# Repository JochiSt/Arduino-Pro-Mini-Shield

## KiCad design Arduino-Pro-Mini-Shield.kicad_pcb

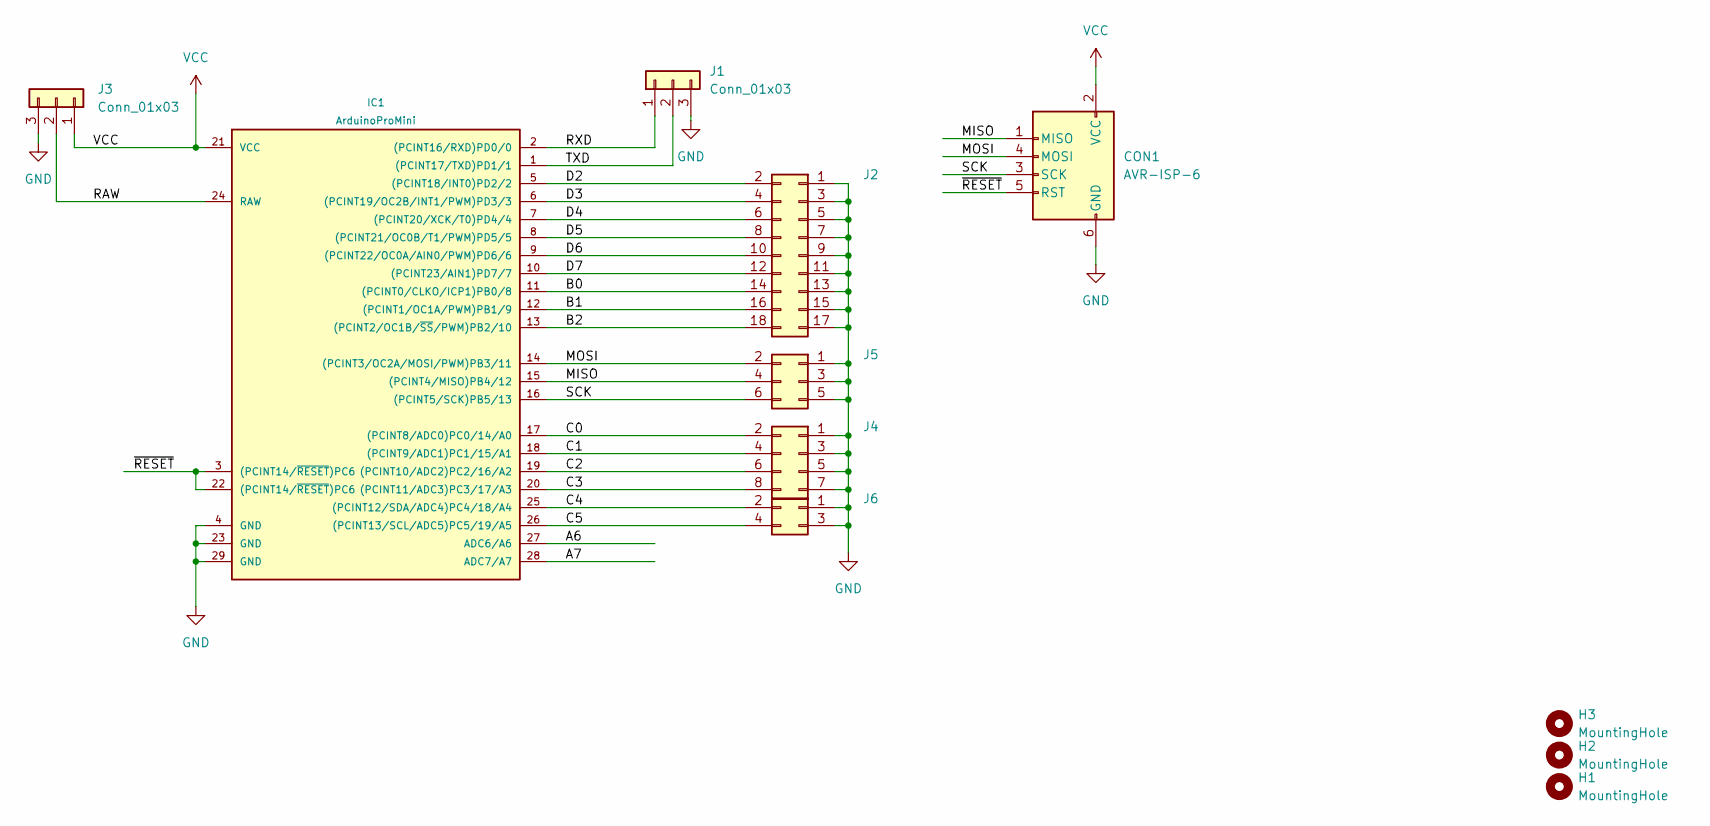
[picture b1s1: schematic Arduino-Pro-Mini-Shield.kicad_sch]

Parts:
CON1: AVR-ISP-6; PinHeader_2x03_P2.54mm_Vertical
H1, H2, H3: MountingHole; MountingHole_3.2mm_M3
IC1: ArduinoProMini; pro_mini
J1, J3: Conn_01x03; PinHeader_1x03_P2.54mm_Vertical
J2: Conn_02x09_Odd_Even; PinHeader_2x09_P2.54mm_Vertical
J4: Conn_02x04_Odd_Even; PinHeader_2x04_P2.54mm_Vertical
J5: Conn_02x03_Odd_Even; PinHeader_2x03_P2.54mm_Vertical
J6: Conn_02x02_Odd_Even; PinHeader_2x02_P2.54mm_Vertical

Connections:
/A6: IC1.27 (ADC6/A6)
/A7: IC1.28 (ADC7/A7)
/B0: IC1.11 ((PCINT0/CLKO/ICP1)PB0/8), J2.14
/B1: IC1.12 ((PCINT1/OC1A/PWM)PB1/9), J2.16
/B2: IC1.13 ((PCINT2/OC1B/~SS/PWM)PB2/10), J2.18
/C0: IC1.17 ((PCINT8/ADC0)PC0/14/A0), J4.2
/C1: IC1.18 ((PCINT9/ADC1)PC1/15/A1), J4.4
/C2: IC1.19 ((PCINT10/ADC2)PC2/16/A2), J4.6
/C3: IC1.20 ((PCINT11/ADC3)PC3/17/A3), J4.8
/C4: IC1.25 ((PCINT12/SDA/ADC4)PC4/18/A4), J6.2
/C5: IC1.26 ((PCINT13/SCL/ADC5)PC5/19/A5), J6.4
/D2: IC1.5 ((PCINT18/INT0)PD2/2), J2.2
/D3: IC1.6 ((PCINT19/OC2B/INT1/PWM)PD3/3), J2.4
/D4: IC1.7 ((PCINT20/XCK/T0)PD4/4), J2.6
/D5: IC1.8 ((PCINT21/OC0B/T1/PWM)PD5/5), J2.8
/D6: IC1.9 ((PCINT22/OC0A/AIN0/PWM)PD6/6), J2.10
/D7: IC1.10 ((PCINT23/AIN1)PD7/7), J2.12
/MISO: CON1.1 (MISO), IC1.15 ((PCINT4/MISO)PB4/12), J5.4
/MOSI: CON1.4 (MOSI), IC1.14 ((PCINT3/OC2A/MOSI/PWM)PB3/11), J5.2
/RAW: IC1.24 (RAW), J3.2
/RXD: IC1.2 ((PCINT16/RXD)PD0/0), J1.1
/SCK: CON1.3 (SCK), IC1.16 ((PCINT5/SCK)PB5/13), J5.6
/TXD: IC1.1 ((PCINT17/TXD)PD1/1), J1.2
/~RESET: CON1.5 (RST), IC1.3 ((PCINT14/~RESET)PC6), IC1.22 ((PCINT14/~RESET)PC6)
GND: CON1.6 (GND), IC1.4 (GND), IC1.23 (GND), IC1.29 (GND), J1.3, J2.1, J2.3, J2.5, J2.7, J2.9, J2.11, J2.13, J2.15, J2.17, J3.3, J4.1, J4.3, J4.5, J4.7, J5.1, J5.3, J5.5, J6.1, J6.3
VCC: CON1.2 (VCC), IC1.21 (VCC), J3.1

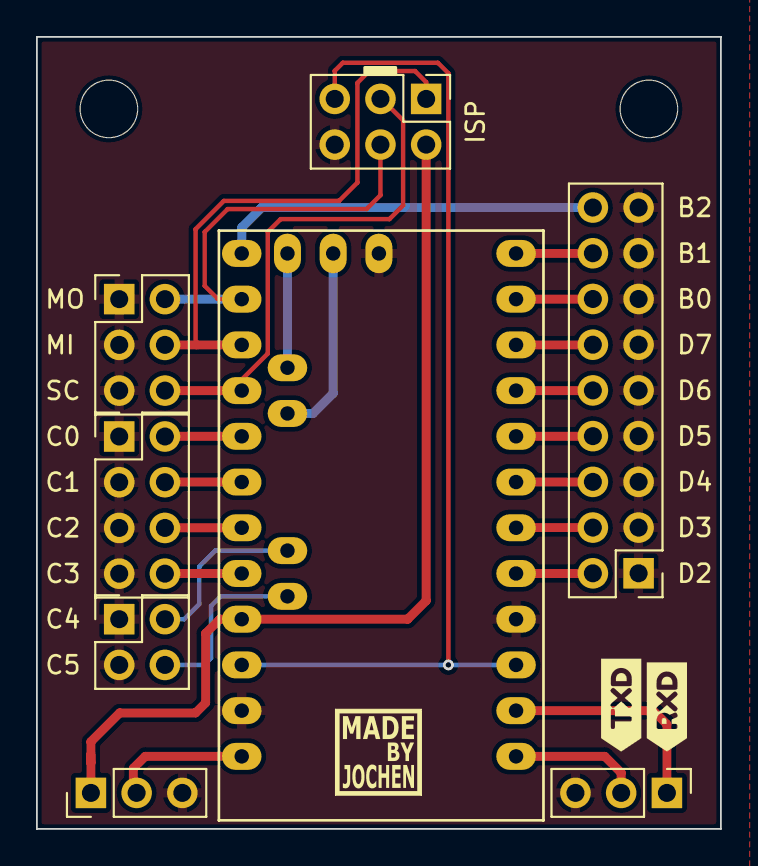
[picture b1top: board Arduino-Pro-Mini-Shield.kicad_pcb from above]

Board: 2 copper layers, 38.0 x 44.0 mm, 12 parts (0 on the bottom side), 24 nets.

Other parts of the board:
kibuzzard-637DE0DD: G***; kibuzzard-637DE0DD
kibuzzard-637DE0EE: G***; kibuzzard-637DE0EE

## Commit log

2022-11-22 added library from MySensors ported to KiCAD 6
    original from https://github.com/mysensors-kicad/mysensors_symbols
2022-11-22 added submodule for Arduino Mini Pro Footprint
2022-11-22 include Arduino Mini Pro
2022-11-23 ignore auto saved files
2022-11-23 added schematic and layout of Arduino Pro Mini Shield
    a development shield to use many pins of the Arduino Pro Mini. An ISP connector can also be populated.
2022-11-23 updated position in schematic of mounting holes
2022-11-23 pushed project for production at AISLER
2023-02-06 BUGFIX: swapped MOSI and MISO
    added also pins for SPI and I2C
2023-02-06 slightly adjusted silkscreen
2023-02-09 updated AISLER to version 3
